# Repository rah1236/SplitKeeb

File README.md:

# SplitKeeb

### SplitKeeb is my custom designed split keyboard based on the QMK Firmware and 2 Arduino Pro Micros.

(No keycaps because I can't afford them at the moment :])

This is a *split* keyboard design, and uses I2C to communicate over a TRRS audio cable (4 poles). 

The parts list is as follows:
* 62 of any Cherry MX style key Switch
* 62 1N4148 Zener Diodes
* 2 identical Resistors from a range of 2.2k Ohms to 10k Ohms (4.7k recommended) 
* 2 Arduino Pro Micros
* 2 PJ-320A TRRS Female Jacks
* 1 TRRS Male to Male wire
* 10 M3 x 8mm Bolts
* 10 M3 nuts

The 2 resistors are for the I2C line, make sure to solder them to whichever board you want to use as the 'main' side.

Make sure to plug in the TRRS cable **BEFORE** you plug in the USB cable, otherwise you risk shorts as the TRRS cable supplies power to the other board.

To program the keyboard, the eaisest method is to use the [QMK Toolbox](https://github.com/qmk/qmk_toolbox), and flash both Pro Micros with the same 'SplitKeeb.hex' file. After both boards have been flashed, plug in the TRRS cable, and then plug in USB, and the keyboard should work as normal. 

Thanks to Rayyan and David for helping me figure out the firmware :)

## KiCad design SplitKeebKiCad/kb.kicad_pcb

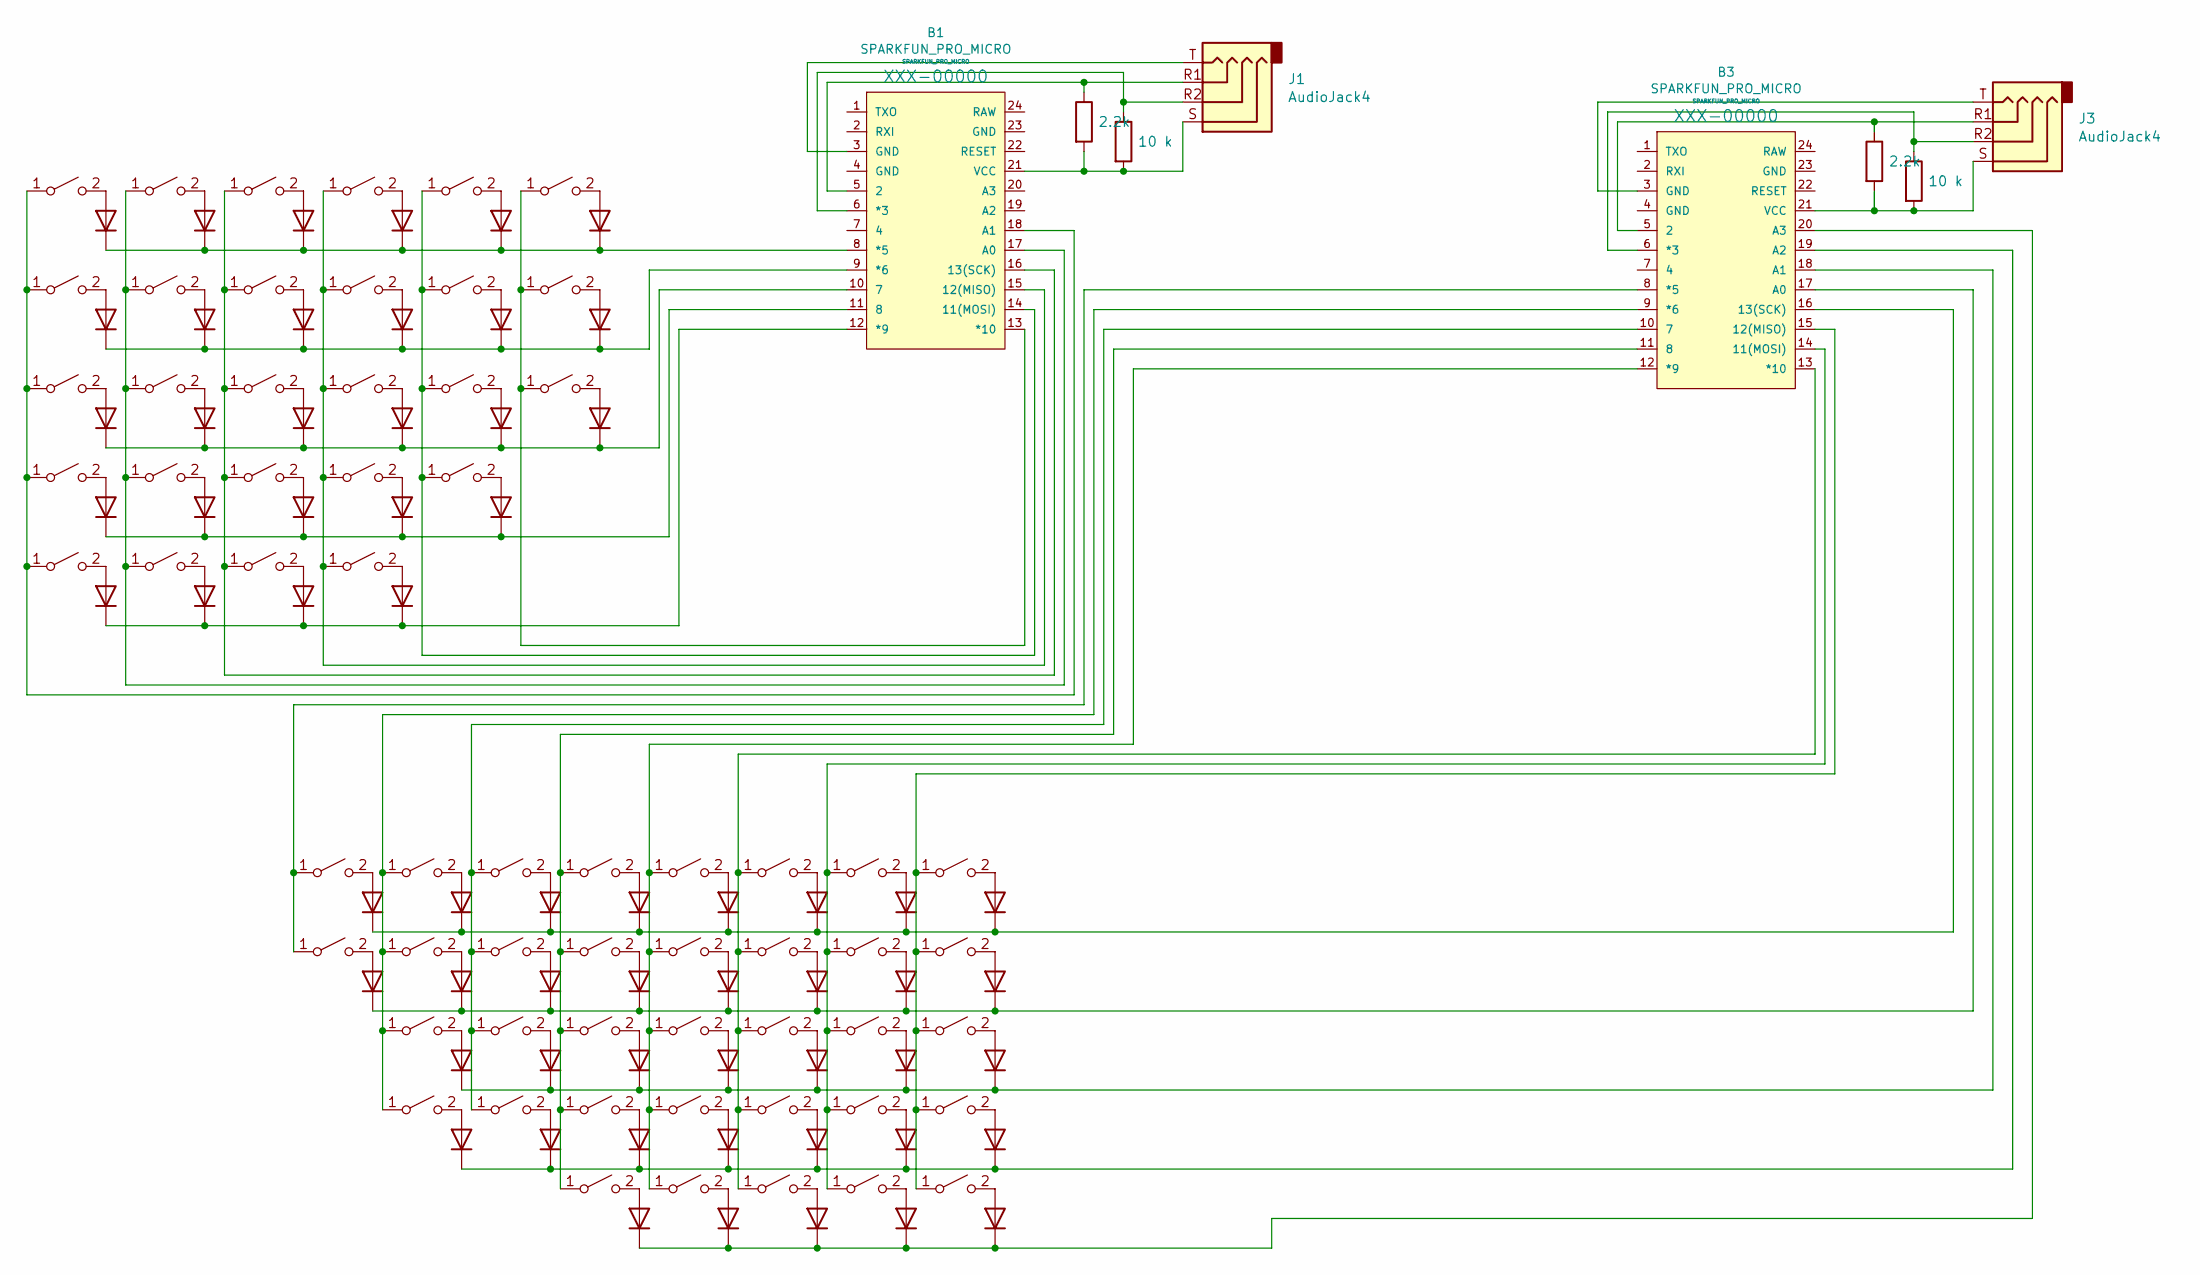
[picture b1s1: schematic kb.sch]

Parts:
A1: Q; SW_Cherry_MX_1.00u_PCB
Alt1: Q; SW_Cherry_MX_1.25u_PCB
B1, B3: SPARKFUN_PRO_MICRO
B2: b; SW_Cherry_MX_1.00u_PCB
Bar1: |; SW_Cherry_MX_1.50u_PCB
Bckspce1: Back; SW_Cherry_MX_2.00u_PCB
C1: Q; SW_Cherry_MX_1.00u_PCB
Caps1: Q; SW_Cherry_MX_1.75u_PCB
Colon1: ;; SW_Cherry_MX_1.00u_PCB
Ctrl1: Q; SW_Cherry_MX_1.25u_PCB
D1, D2, D3, D4, D5, D6, D7, D8, D9, D10, D11, D12, D13, D14, D15, D16, D17, D18, D19, D20, D21, D22, D23, D24, D25, D26, D27, D29, D30, D31, D32, D33, D34, D35, D36, D37, D38, D39, D40, D41, D42, D43, D44, D45, D46, D47, D48, D49, D50, D51, D52, D53, D54, D55, D56, D57, D58, D59, D60, D61, D62, D63: 1N4148; D_DO-35_SOD27_P7.62mm_Horizontal
D28: Q; SW_Cherry_MX_1.00u_PCB
E1: Q; SW_Cherry_MX_1.00u_PCB
Eight1: 8; SW_Cherry_MX_1.00u_PCB
Enter1: enter; SW_Cherry_MX_2.25u_PCB
EqualsSign1: =+; SW_Cherry_MX_1.00u_PCB
F1: Q; SW_Cherry_MX_1.00u_PCB
Five1: Q; SW_Cherry_MX_1.00u_PCB
Four1: Q; SW_Cherry_MX_1.00u_PCB
G1: Q; SW_Cherry_MX_1.00u_PCB
H1: h; SW_Cherry_MX_1.00u_PCB
I1: i; SW_Cherry_MX_1.00u_PCB
J1, J3: AudioJack4; TRRS-PJ-320A
J2: j; SW_Cherry_MX_1.00u_PCB
K1: k; SW_Cherry_MX_1.00u_PCB
L1: l; SW_Cherry_MX_1.00u_PCB
LeftAligator1: <; SW_Cherry_MX_1.00u_PCB
LeftBracket1: [; SW_Cherry_MX_1.00u_PCB
M1: m; SW_Cherry_MX_1.00u_PCB
MenuButton1: Menu; SW_Cherry_MX_1.25u_PCB
N1: n; SW_Cherry_MX_1.00u_PCB
Nine1: 9; SW_Cherry_MX_1.00u_PCB
O1: o; SW_Cherry_MX_1.00u_PCB
One1: 1; SW_Cherry_MX_1.00u_PCB
P1: p; SW_Cherry_MX_1.00u_PCB
Q1: Q; SW_Cherry_MX_1.00u_PCB
QuestionMark1: ?; SW_Cherry_MX_1.00u_PCB
QuoteSign1: \"; SW_Cherry_MX_1.00u_PCB
R1, R4: 2.2k; R_Axial_DIN0207_L6.3mm_D2.5mm_P7.62mm_Horizontal
R2, R5: 10 k; R_Axial_DIN0207_L6.3mm_D2.5mm_P7.62mm_Horizontal
R3: Q; SW_Cherry_MX_1.00u_PCB
RightAlligaotr1: >; SW_Cherry_MX_1.00u_PCB
RightAlt1: RAlt; SW_Cherry_MX_1.25u_PCB
RightBracket1: ]; SW_Cherry_MX_1.00u_PCB
RightCtrl1: RCTRL; SW_Cherry_MX_1.25u_PCB
RightShift1: RShift; SW_Cherry_MX_2.75u_PCB
RightSpace1: RSpace; SW_Cherry_MX_1.00u_PCB
RightWindows1: RWindows; SW_Cherry_MX_1.25u_PCB
S1: Q; SW_Cherry_MX_1.00u_PCB
Seven1: 7; SW_Cherry_MX_1.00u_PCB
Shift1: Q; SW_Cherry_MX_2.25u_PCB
Six1: 6; SW_Cherry_MX_1.00u_PCB
Space1: Q; SW_Cherry_MX_1.00u_PCB
T1: Q; SW_Cherry_MX_1.00u_PCB
Tab1: esc; SW_Cherry_MX_1.50u_PCB
Two1: Q; SW_Cherry_MX_1.00u_PCB
U1: u; SW_Cherry_MX_1.00u_PCB
UnderScore1: _; SW_Cherry_MX_1.00u_PCB
V1: Q; SW_Cherry_MX_1.00u_PCB
W1: Q; SW_Cherry_MX_1.00u_PCB
Windows1: Q; SW_Cherry_MX_1.25u_PCB
X1: Q; SW_Cherry_MX_1.00u_PCB
Y1: y; SW_Cherry_MX_1.00u_PCB
Z1: Q; SW_Cherry_MX_1.00u_PCB
Zero1: 0; SW_Cherry_MX_1.00u_PCB
esc1: esc; SW_Cherry_MX_1.00u_PCB
three1: Q; SW_Cherry_MX_1.00u_PCB

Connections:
unnamed: A1.1 (A), B1.17 (A0), One1.1 (A), Q1.1 (A), Windows1.1 (A), Z1.1 (A)
unnamed: A1.2 (B), D8.2 (A)
unnamed: Alt1.1 (A), B1.16 (13(SCK)), S1.1 (A), Two1.1 (A), W1.1 (A), X1.1 (A)
unnamed: Alt1.2 (B), D15.2 (A)
unnamed: B1.5 (2), J1.R1, R1.1
unnamed: B1.6 (*3), J1.R2, R2.1
unnamed: B1.8 (*5), D1.1 (K), D6.1 (K), D11.1 (K), D16.1 (K), D21.1 (K), D25.1 (K)
unnamed: B1.9 (*6), D2.1 (K), D7.1 (K), D12.1 (K), D17.1 (K), D22.1 (K), D26.1 (K)
unnamed: B1.10 (7), D3.1 (K), D8.1 (K), D13.1 (K), D18.1 (K), D23.1 (K), D27.1 (K)
unnamed: B1.11 (8), D4.1 (K), D9.1 (K), D14.1 (K), D19.1 (K), D24.1 (K)
unnamed: B1.12 (*9), D5.1 (K), D10.1 (K), D15.1 (K), D20.1 (K)
unnamed: B1.13 (*10), Five1.1 (A), G1.1 (A), T1.1 (A)
unnamed: B1.14 (11(MOSI)), F1.1 (A), Four1.1 (A), R3.1 (A), V1.1 (A)
unnamed: B1.15 (12(MISO)), C1.1 (A), D28.1 (A), E1.1 (A), Space1.1 (A), three1.1 (A)
unnamed: B1.18 (A1), Caps1.1 (A), Ctrl1.1 (A), Shift1.1 (A), Tab1.1 (A), esc1.1 (A)
unnamed: B1.21 (VCC), J1.S, R1.2, R2.2
unnamed: B2.1 (A), B3.9 (*6), H1.1 (A), Seven1.1 (A), U1.1 (A)
unnamed: B2.2 (B), D34.2 (A)
unnamed: B3.5 (2), J3.R1, R4.1
unnamed: B3.6 (*3), J3.R2, R5.1
unnamed: B3.8 (*5), Six1.1 (A), Y1.1 (A)
unnamed: B3.10 (7), Eight1.1 (A), I1.1 (A), J2.1 (A), N1.1 (A)
unnamed: B3.11 (8), K1.1 (A), M1.1 (A), Nine1.1 (A), O1.1 (A), RightSpace1.1 (A)
unnamed: B3.12 (*9), L1.1 (A), LeftAligator1.1 (A), P1.1 (A), RightAlt1.1 (A), Zero1.1 (A)
unnamed: B3.13 (*10), Colon1.1 (A), LeftBracket1.1 (A), RightAlligaotr1.1 (A), RightWindows1.1 (A), UnderScore1.1 (A)
unnamed: B3.14 (11(MOSI)), EqualsSign1.1 (A), MenuButton1.1 (A), QuestionMark1.1 (A), QuoteSign1.1 (A), RightBracket1.1 (A)
unnamed: B3.15 (12(MISO)), Bar1.1 (A), Bckspce1.1 (A), Enter1.1 (A), RightCtrl1.1 (A), RightShift1.1 (A)
unnamed: B3.16 (13(SCK)), D29.1 (K), D31.1 (K), D35.1 (K), D39.1 (K), D44.1 (K), D49.1 (K), D54.1 (K), D59.1 (K)
unnamed: B3.17 (A0), D30.1 (K), D32.1 (K), D36.1 (K), D40.1 (K), D45.1 (K), D50.1 (K), D55.1 (K), D60.1 (K)
unnamed: B3.18 (A1), D33.1 (K), D37.1 (K), D41.1 (K), D46.1 (K), D51.1 (K), D56.1 (K), D61.1 (K)
unnamed: B3.19 (A2), D34.1 (K), D38.1 (K), D42.1 (K), D47.1 (K), D52.1 (K), D57.1 (K), D62.1 (K)
unnamed: B3.20 (A3), D43.1 (K), D48.1 (K), D53.1 (K), D58.1 (K), D63.1 (K)
unnamed: B3.21 (VCC), J3.S, R4.2, R5.2
unnamed: Bar1.2 (B), D60.2 (A)
unnamed: Bckspce1.2 (B), D59.2 (A)
unnamed: C1.2 (B), D19.2 (A)
unnamed: Caps1.2 (B), D3.2 (A)
unnamed: Colon1.2 (B), D51.2 (A)
unnamed: Ctrl1.2 (B), D5.2 (A)
unnamed: D1.2 (A), esc1.2 (B)
unnamed: D2.2 (A), Tab1.2 (B)
unnamed: D4.2 (A), Shift1.2 (B)
unnamed: D6.2 (A), One1.2 (B)
unnamed: D7.2 (A), Q1.2 (B)
unnamed: D9.2 (A), Z1.2 (B)
unnamed: D10.2 (A), Windows1.2 (B)
unnamed: D11.2 (A), Two1.2 (B)
unnamed: D12.2 (A), W1.2 (B)
unnamed: D13.2 (A), S1.2 (B)
unnamed: D14.2 (A), X1.2 (B)
unnamed: D16.2 (A), three1.2 (B)
unnamed: D17.2 (A), E1.2 (B)
unnamed: D18.2 (A), D28.2 (B)
unnamed: D20.2 (A), Space1.2 (B)
unnamed: D21.2 (A), Four1.2 (B)
unnamed: D22.2 (A), R3.2 (B)
unnamed: D23.2 (A), F1.2 (B)
unnamed: D24.2 (A), V1.2 (B)
unnamed: D25.2 (A), Five1.2 (B)
unnamed: D26.2 (A), T1.2 (B)
unnamed: D27.2 (A), G1.2 (B)
unnamed: D29.2 (A), Six1.2 (B)
unnamed: D30.2 (A), Y1.2 (B)
unnamed: D31.2 (A), Seven1.2 (B)
unnamed: D32.2 (A), U1.2 (B)
unnamed: D33.2 (A), H1.2 (B)
unnamed: D35.2 (A), Eight1.2 (B)
unnamed: D36.2 (A), I1.2 (B)
unnamed: D37.2 (A), J2.2 (B)
unnamed: D38.2 (A), N1.2 (B)
unnamed: D39.2 (A), Nine1.2 (B)
unnamed: D40.2 (A), O1.2 (B)
unnamed: D41.2 (A), K1.2 (B)
unnamed: D42.2 (A), M1.2 (B)
unnamed: D43.2 (A), RightSpace1.2 (B)
unnamed: D44.2 (A), Zero1.2 (B)
unnamed: D45.2 (A), P1.2 (B)
unnamed: D46.2 (A), L1.2 (B)
unnamed: D47.2 (A), LeftAligator1.2 (B)
unnamed: D48.2 (A), RightAlt1.2 (B)
unnamed: D49.2 (A), UnderScore1.2 (B)
unnamed: D50.2 (A), LeftBracket1.2 (B)
unnamed: D52.2 (A), RightAlligaotr1.2 (B)
unnamed: D53.2 (A), RightWindows1.2 (B)
unnamed: D54.2 (A), EqualsSign1.2 (B)
unnamed: D55.2 (A), RightBracket1.2 (B)
unnamed: D56.2 (A), QuoteSign1.2 (B)
unnamed: D57.2 (A), QuestionMark1.2 (B)
unnamed: D58.2 (A), MenuButton1.2 (B)
unnamed: D61.2 (A), Enter1.2 (B)
unnamed: D62.2 (A), RightShift1.2 (B)
unnamed: D63.2 (A), RightCtrl1.2 (B)

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
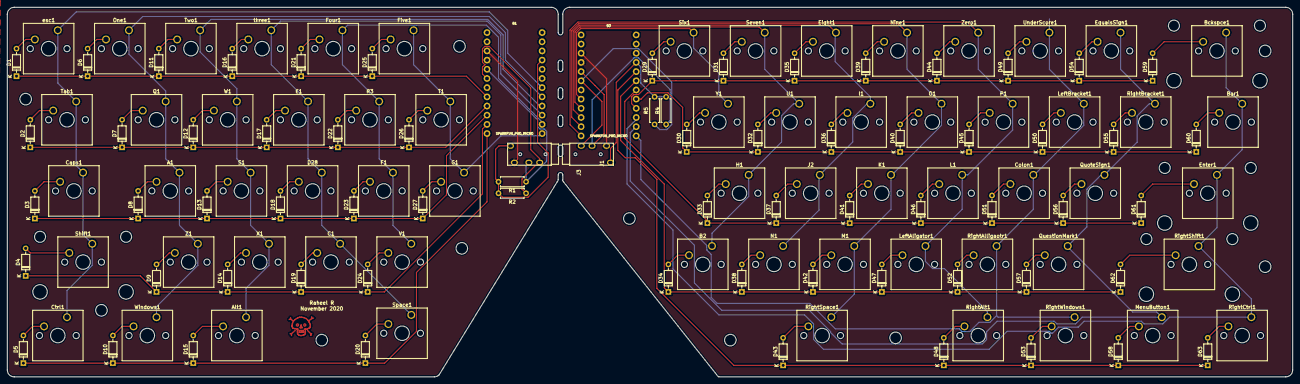
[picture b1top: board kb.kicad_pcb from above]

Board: 2 copper layers, 355.6 x 102.2 mm, 143 parts (0 on the bottom side), 94 nets.

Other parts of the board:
 : MountingHole_3.2mm_M3
 #2,  #3,  #4,  #5,  #6,  #7,  #8,  #9,  #10: MountingHole_3.2mm_M3
 #11: Symbol_Danger_CopperTop_Small

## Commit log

2021-04-20 Uploaded GRBR FIles
2021-04-20 Added KiCad files and Hex files
2021-04-20 Added Readme
2021-04-20 added 3d printable cases and uncompiled firmware
